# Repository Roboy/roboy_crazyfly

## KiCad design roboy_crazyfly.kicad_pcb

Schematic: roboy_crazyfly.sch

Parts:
C1, C2, C3, C4, C7: 100n; C_0402
C5: 10n; C_0402
C6: 1u; C_0402
C8, C9: 4.7u; C_0402
D1, D2, D3, D4: BAT54; C_0402
D5, D6, D7, D8, D9: LED; LED_0603
P1: MICRO_B_USB; USB_Micro-B_Molex_47346-0001
P2: CONN_BAT; Socket_Strip_Straight_1x02
P3: CONN_01X06; Socket_Strip_Straight_1x06
P4: CONN_01X04; Socket_Strip_Straight_1x04
P5, P6: CONN_01X10; Socket_Strip_Straight_1x10
P7, P8, P9, P10: CONN_01X02; JST-2-pin-female-side
Q1, Q2, Q3, Q4: PMV30UN2; SOT-23
R1, R25, R26, R27, R28: 10k; R_0402
R2, R5, R8: 47; R_0402
R3, R7: 100; R_0402
R4, R6, R9, R10: 2.2k; R_0402
R29, R30, R31, R32: 100k; R_0402
U1: STM32F405; LQFP-64_10x10mm_Pitch0.5mm
U2: 24AA64FT-E/OT; SOT-23-5
Y1: Crystal; CRYSTAL_8MHZ

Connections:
+BATT: D1.1 (K), D2.1 (K), D3.1 (K), D4.1 (K), P2.1, P7.2, P8.2, P9.2, P10.2; also elsewhere on the board
/E_CS0: P5.9, U1.53
/E_CS1: P5.8, U1.56
/E_CS2: P5.7, U1.57
/E_CS3: P5.6, U1.61
/E_MISO: P6.4, U1.22
/E_MOSI: P6.5, U1.23
/E_NRF_IO1: P6.7
/E_NRF_IO2: P6.6
/E_OW/WKUP: P6.8
/E_RX1: P5.2, U1.52
/E_RX2: P6.2, U1.17
/E_SCK: P6.3, U1.21
/E_SCL: P5.5, R9.2, U1.58, U2.1 (scl)
/E_SDA: P5.4, R10.2, U1.59, U2.3 (sda)
/E_TX1: P5.3, U1.51
/E_TX2: P6.1, U1.16
/IMU_SCL: R6.2, U1.41; also elsewhere on the board
/IMU_SDA: R4.2, U1.40; also elsewhere on the board
/LED_BLUE_L: R2.1, U1.54
/LED_GREEN_L: R5.2, U1.9
/LED_GREEN_R: R8.2, U1.10
/LED_RED_L: R3.1, U1.8
/LED_RED_R: R7.2, U1.11
/MOTOR1: R29.2, U1.15
/MOTOR2: R30.2, U1.30
/MOTOR3: R31.2, U1.50
/MOTOR4: R32.2, U1.62
/MPU_FSYNC: U1.3; also elsewhere on the board
/MPU_INT: U1.2
/NRF_FLOW_CTRL: U1.20
/NRF_RX: U1.37
/NRF_SWCLK: P4.1, U1.34
/NRF_SWIO: P4.4, U1.36
/NRF_TX: U1.38
/STM_BOOT0: R1.1, U1.60
/STM_NRST: C7.1, P3.2, U1.7
/STM_STO: P3.1
/STM_SW0: U1.55
/STM_SWCLK: P3.5, U1.49
/STM_SWIO: P3.3, U1.46
/VUSB: P1.1, P6.10
/V_COM_EXP: P6.9
GDN: D5.1 (K)
GND: C1.2, C2.2, C3.2, C4.2, C5.2, C6.2, C7.2, C8.2, C9.2, P1.5, P2.2, P3.4, P4.3, P5.10, Q1.1 (S), Q2.1 (S), Q3.1 (S), Q4.1 (S), R1.2, R25.2, R26.2, R27.2, R28.2, U1.12, U1.18, U1.28, U1.63, U2.2 (VSS), U2.5 (wp); also elsewhere on the board
unnamed: C8.1, U1.31
unnamed: C9.1, U1.47
unnamed: D1.2 (A), P7.1, Q1.3 (D)
unnamed: D2.2 (A), P8.1, Q2.3 (D)
unnamed: D3.2 (A), P9.1, Q3.3 (D)
unnamed: D4.2 (A), P10.1, Q4.3 (D)
unnamed: D5.2 (A), R2.2
unnamed: D6.1 (K), R3.2
unnamed: D7.1 (K), R5.1
unnamed: D8.1 (K), R7.1
unnamed: D9.1 (K), R8.1
unnamed: P1.2, U1.44
unnamed: P1.3, U1.45
unnamed: P1.4, U1.43
unnamed: Q1.2 (G), R25.1, R29.1
unnamed: Q2.2 (G), R26.1, R30.1
unnamed: Q3.2 (G), R27.1, R31.1
unnamed: Q4.2 (G), R28.1, R32.1
unnamed: U1.5, Y1.1
unnamed: U1.6, Y1.2
VCC: C1.1, C2.1, C3.1, C4.1, C5.1, C6.1, D6.2 (A), D7.2 (A), D8.2 (A), D9.2 (A), P3.6, P5.1, R4.1, R6.1, R9.1, R10.1, U1.13, U1.19, U1.32, U1.48, U1.64, U2.4 (vcc); also elsewhere on the board
VCCNRF: P4.2, U1.1; also elsewhere on the board

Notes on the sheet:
I2C address 1010000b
U1 decoupling: 100n on each VDD 10n and 4.7u on VDDA

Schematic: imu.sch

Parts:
C10, C13, C14: 100n; C_0402
C11: 4.7u; C_0402
C12: 10n; C_0402
U3: MPU9250; mpu9250
U4: LPS25H

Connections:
/IMU_SCL: U3.23; also elsewhere on the board
/IMU_SDA: U3.24; also elsewhere on the board
/MPU_FSYNC: U3.11; also elsewhere on the board
GND: C10.2, C11.2, C12.2, C13.2, C14.2, U3.18, U3.20, U4.3, U4.8, U4.9; also elsewhere on the board
unnamed: U3.7, U4.2
unnamed: U3.21, U4.4
VCCA: C10.1, C11.1, C12.1, C13.1, C14.1, U3.1, U3.8, U3.9, U3.10, U3.13, U3.22, U4.1, U4.5, U4.6, U4.10; also elsewhere on the board

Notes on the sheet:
I2C address 1101001b
I2C address 1011101b

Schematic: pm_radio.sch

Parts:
C15, C26, C31, C32, C34: 4.7u; C_0402
C16, C17, C18, C19, C22: 100n; C_0402
C20: 22uF; 22uF-elektrolyt-kondensator
C21: 47n; C_0402
C23: 2.2n; C_0402
C24, C35: 1u; C_0402
C25, C30: 12p; C_0402
C27, C29: 10n; C_0402
C28: 220p; C_0402
C33: 2.2p; C_0402
D10: LED; LED_0603
L1: 1uH; C_0402
L2: 1nH; C_0402
L3: 3.9nH; C_0402
R11: 200k; R_0402
R12, R13, R18, R20: 10k; R_0402
R14: 47; R_0402
R15, R17, R19, R21, R22, R24: 1k; R_0402
R16: 100k; R_0402
R23: 0; R_0402
SW1: SW_PUSH; switch_tactile
U5: NRF51822; UQFN-48-1EP_6x6mm_Pitch0.4mm
U6: BQ24075; QFN-16-1EP_3x3mm_Pitch0.5mm
U7: BALUN; BALUN_WIFI_BLUETOOTH
U8: NCP702SN30; TSOP-5_1.65x3.05mm_Pitch0.95mm
U9: LP2985-30; SOT-23-5
U10: SiP32431; SC-70-6
U11: RFX2401C; QFN-16-1EP_3x3mm_Pitch0.5mm
U12: antenna; RF_ANTENNA
U13: TSX-3225; SMD_CRYSTALL_TSX-3225

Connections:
+BATT: C20.1, R11.2, U6.2, U6.3; also elsewhere on the board
/pm_radio/ANT+: U5.31, U7.4
/pm_radio/ANT-: U5.32, U7.3
/pm_radio/E_NRF_IO1: U5.18
/pm_radio/E_NRF_IO2: U5.17
/pm_radio/E_OW/WKUP: R15.2, U5.14
/pm_radio/LED_BLUE: R14.2, U5.19
/pm_radio/NRF_FLOW_CTRL: U5.20
/pm_radio/NRF_RX: U5.3
/pm_radio/NRF_SWCLK: U5.24
/pm_radio/NRF_SWIO: U5.23
/pm_radio/NRF_TX: U5.48
/pm_radio/OW_PU: R15.1, U5.15
/pm_radio/PA_RX_EN: R21.1
/pm_radio/PA_TX_DIS: U5.28
/pm_radio/PM_CHG: U5.4, U6.9
/pm_radio/PM_CHG_EN: U5.11, U6.4
/pm_radio/PM_EN1: U5.9, U6.6
/pm_radio/PM_EN2: U5.10, U6.5
/pm_radio/PM_ISET: R19.1, U5.7, U6.16
/pm_radio/PM_PGOOD: U5.8, U6.7
/pm_radio/STM_BOOT0: U5.41
/pm_radio/STM_NRST: U5.40
/pm_radio/STM_SWCLK: U5.47
/pm_radio/STM_SWIO: R22.1, U5.43
/pm_radio/SWITCH: SW1.1, U5.25
/pm_radio/VBAT: C19.2, R11.1, R16.2, U5.5
/pm_radio/VBAT_SINK: C19.1, R16.1, U5.6
/pm_radio/VCOM_EXP: U10.1
/pm_radio/VEN_D: R12.2, R13.1, U5.16, U9.3, U10.4
/pm_radio/VUSB: C15.1, R12.1, U6.13
GND: C15.2, C20.2, C21.2, C22.2, C23.2, C24.2, C25.2, C26.2, C27.2, C28.2, C29.2, C30.2, C31.2, C32.2, C34.2, C35.2, D10.1 (K), L2.2, R13.2, R17.2, R18.2, R19.2, R20.2, SW1.2, U5.13, U5.33, U5.34, U5.49, U6.8, U6.15, U6.17, U7.5, U8.2, U9.2, U10.2, U11.1, U11.2, U11.3, U11.7, U11.8, U11.9, U11.11, U11.12, U11.15, U11.17, U13.2 (GND), U13.4 (GND); also elsewhere on the board
unnamed: C16.2, C17.2, C18.2
unnamed: C21.1, U5.29
unnamed: C22.1, U5.39
unnamed: C23.1, R24.2, U5.30, U7.2
unnamed: C25.1, U5.37, U13.1 (OSC1)
unnamed: C29.1, U9.4
unnamed: C30.1, U5.38, U13.3 (OSC2)
unnamed: C33.1, L2.1, L3.2
unnamed: C33.2, U11.10
unnamed: D10.2 (A), R14.1
unnamed: L3.1, U12.1
unnamed: R17.1, U6.12
unnamed: R18.1, U6.14
unnamed: R20.1, U6.1
unnamed: R21.2, U5.27
unnamed: R22.2, U5.44
unnamed: R24.1, U11.5
unnamed: U7.1, U11.4
VCC: C31.1, L1.1, U9.5; also elsewhere on the board
VCCA: C32.1, L1.2; also elsewhere on the board
VCCNRF: C16.1, C17.1, C18.1, C26.1, C27.1, C28.1, C35.1, U5.1, U5.12, U5.35, U5.36, U8.5, U11.14, U11.16; also elsewhere on the board
VCOM: C24.1, C34.1, U6.10, U8.1, U8.3, U9.1, U10.3

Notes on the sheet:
Fast charge: 0.98A Input current limit: 1.55A
Filter the power supply at 73kHz should filter most of the PWM L1 shall support at least 20mA to power the IMU
Analog power only used by IMU. Inductance and capacitor placed near IMU

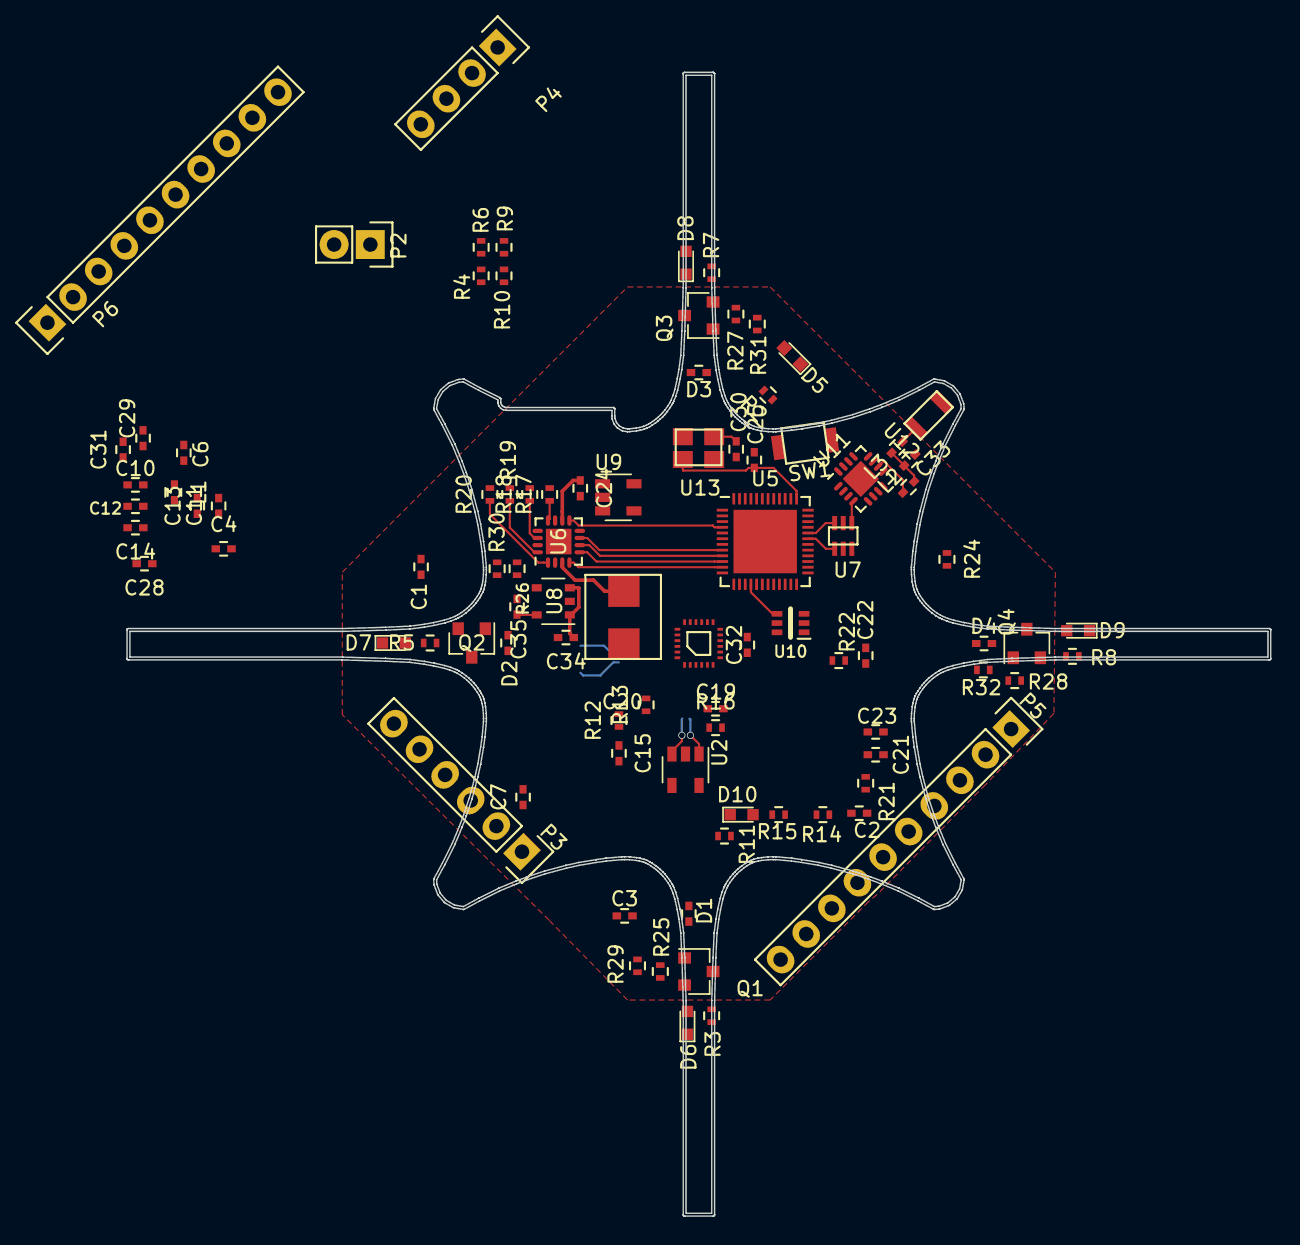
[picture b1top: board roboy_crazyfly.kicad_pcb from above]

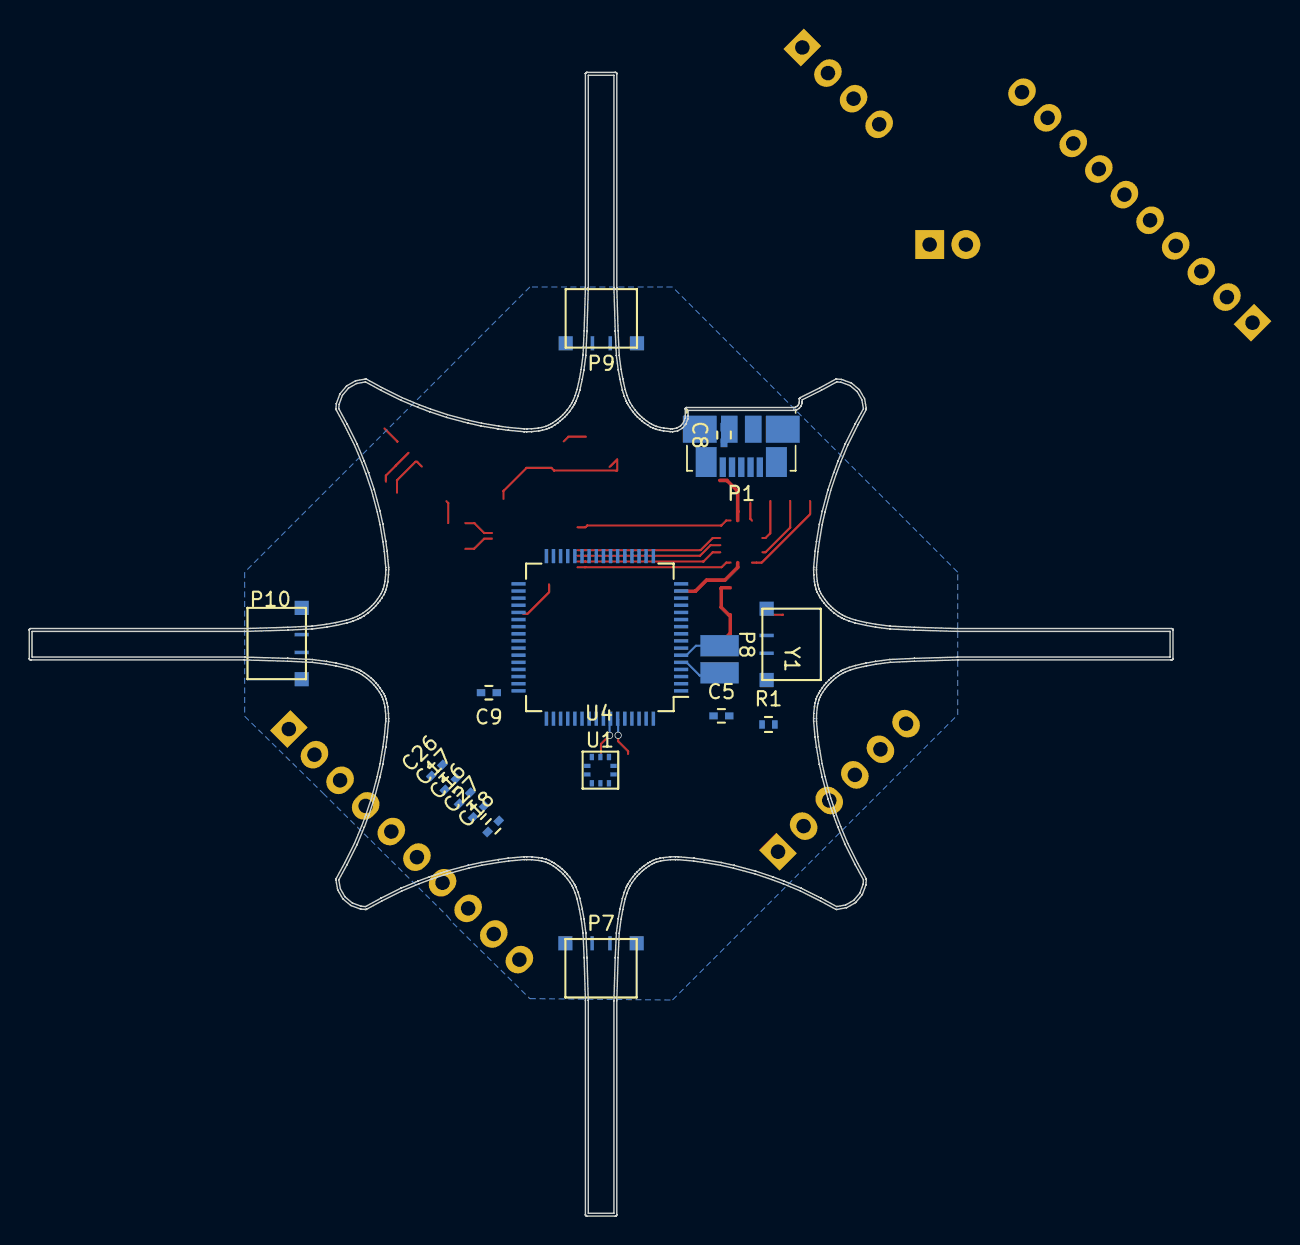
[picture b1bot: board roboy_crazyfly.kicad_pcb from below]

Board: 4 copper layers, 80.2 x 80.2 mm, 108 parts (17 on the bottom side), 95 nets.

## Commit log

2018-02-15 microcontoller schematics
2018-02-15 almost done with schematics
2018-02-18 done with pcb outline
2018-02-18 with correct footprints
2018-02-18 moved micro usb to side
2018-02-18 added 22uF elektorlyt condensator
2018-02-18 with current BOM
2018-02-21 rerouting
